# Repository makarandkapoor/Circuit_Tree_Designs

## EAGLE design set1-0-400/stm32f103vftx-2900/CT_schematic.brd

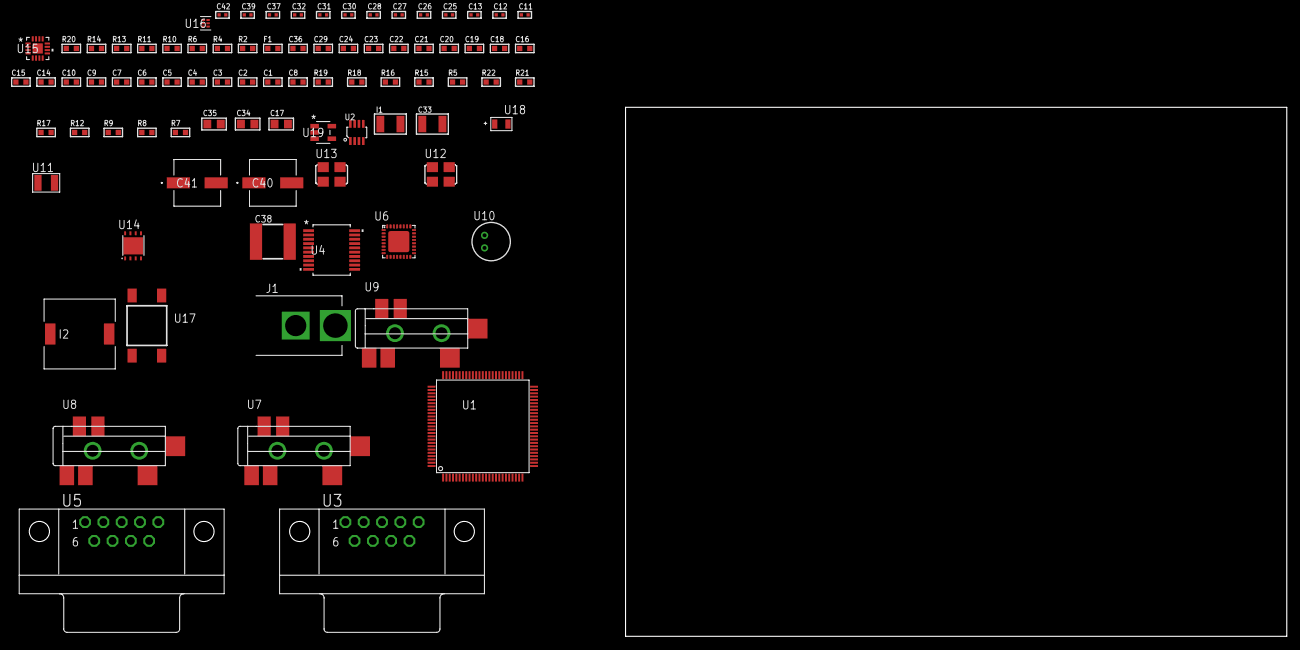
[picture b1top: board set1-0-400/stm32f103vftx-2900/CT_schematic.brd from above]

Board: 2 copper layers, 100.0 x 80.0 mm, 85 parts (0 on the bottom side), 58 nets, no tracks yet.

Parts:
C1, C10, C14, C15, C16, C18, C19, C20, C21, C22, C23, C24, C29, C36: 1e-06; C0603
C2, C3, C4, C5, C6, C7: 1e-07; C0603
C8: 4.7e-06; C0603
C9: 1e-08; C0603
C11, C12: 1e-11; C0402
C13, C25, C26, C27, C28, C37, C39: 1e-07; C0402
C17: 4.7e-06; C0805
C30, C31, C32, C42: 1e-08; C0402
C33: 1e-05; C1210
C34, C35: 1e-05; C0805
C38: 6.8e-05; 2220
C40, C41: 0.0001; EXV-9H
F1: 240.0; L0603
I1: 1.5e-05; L1210
I2: 5.2e-06; DR1040
J1: PJ-037B; PJ-037B_PACKAGE
R2, R14: 1000.0; R0603
R4: 4700.0; R0603
R5, R18, R19: 10000.0; R0603
R6: 120.0; R0603
R7, R8, R9, R12: 100000.0; R0603
R10, R11: 1270.0; R0603
R13: 200.0; R0603
R15: 20000.0; R0603
R16: 91000.0; R0603
R17: 300000.0; R0603
R20: 9100.0; R0603
R21: 680000.0; R0603
R22: 120000.0; R0603
U1: stm32f103vft7; LQFP100
U2: MAX3051EKA+T; SOT-23-8
U3, U5: 182-009-113R531; 182-009-MALE
U4: MAX3218EAP+T; SSOP-20
U6: SGTL5000XNAA3; QFN-32
U7, U8, U9: SJ-43515TS-SMT-TR
U10: WM-64PCT; WM-64PC
U11: ABS07-32.768KHZ-7-T
U12: ASFL-24.57MHZ-NCS; ASFL1
U13: ASFL1-25MHZ-NCS; ASFL1
U14: LP3878SDX-ADJ/NOPB; WSON-8
U15: LTC3601EUD#PBF; QFN-16_EP
U16: TPS3895ADRYR; SON-6
U17: 4-1437565-2; SW_4-1437565-2
U18: Q65110A2395; LGM67K-G1J2-24-Z
U19: nc7sz125m5x; NC7SZ125M5X

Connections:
CLK_CRYSTAL_U1_8: C11.1, U1.8, U11.1
CLK_CRYSTAL_U1_9: C12.1, U1.9, U11.2
CLK_U1_12: U1.12, U13.3
CLK_U6_21: U6.21, U12.3
GND: C1.2, C2.2, C3.2, C4.2, C5.2, C6.2, C7.2, C8.2, C9.2, C10.2, C11.2, C12.2, C13.2, C14.2, C15.2, C16.2, C25.2, C26.2, C27.2, C28.2, C29.2, C30.2, C31.2, C32.2, C33.2, C34.2, C35.2, C36.2, C38.1, C38.2, C39.2, C40.2, C41.2, C42.2, J1.2, R2.2, R5.2, R11.2, R14.2, R15.2, R17.2, R20.2, R22.2, U1.10, U1.19, U1.20, U1.27, U1.49, U1.74, U1.99, U2.2, U2.8, U3.5, U4.5, U4.17, U4.20, U5.5, U6.1, U6.3, U6.7, U6.EXP, U8.1, U9.1, U10.2, U12.2, U13.2, U14.3, U14.PAD, U15.1, U15.9, U15.17, U16.2, U18.C, U19.1, U19.3
NET_U1_14: R4.1, U1.14, U19.4
NET_U1_22: C9.1, C10.1, F1.1, U1.21, U1.22
NET_U1_94: R5.1, U1.94
NET_U1_98: U17.3, U17.4
NET_U2_6: R6.2, U2.6
NET_U3_2: R6.2, U2.6, U3.2
NET_U3_3: R6.1, U2.7, U3.3
NET_U4_1: I1.1, U4.1
NET_U4_2: R7.1, U4.2
NET_U4_3: R8.1, U4.3
NET_U4_4: R9.1, U4.4
NET_U4_15: C16.1, U4.15
NET_U4_16: C17.2, U4.16
NET_U4_18: C17.1, U4.18
NET_U4_19: C15.1, U4.19
NET_U5_2: U4.12, U5.2
NET_U5_3: U4.14, U5.3
NET_U5_7: U4.11, U5.7
NET_U5_8: U4.13, U5.8
NET_U6_10: C28.1, U6.10
NET_U6_29: R10.1, U6.29
NET_U6_31: R11.1, U6.31
NET_U7_1: U6.4, U7.1
NET_U7_2: U6.2, U7.2
NET_U7_5: U6.6, U7.5
NET_U8_2: C19.1, U8.2
NET_U8_5: C18.1, U8.5
NET_U9_2: C21.1, C22.1, U9.2
NET_U9_5: C20.1, U9.5
NET_U9_13: C21.2, C22.2
NET_U10_1: C23.1, C24.1, C29.1, U6.16, U10.1
NET_U10_15: C23.2, C24.2
NET_U14_1: C32.1, U14.1
NET_U14_6: R13.2, R14.1, U14.6
NET_U14_8: R12.1, U14.8
NET_U15_3: C37.2, I2.1, U15.3, U15.4
NET_U15_6: C37.1, U15.6
NET_U15_7: C36.1, U15.7, U15.12
NET_U15_10: R17.1, U15.10
NET_U15_11: R15.1, R16.1, U15.11
NET_U15_ATNET_3: I2.2, R16.2
NET_U16_1: R19.1, R20.1, U16.1
NET_U16_3: R21.2, R22.1, U16.3
NET_U16_4: R18.1, U16.4, U19.2
NET_U17_1: R2.1, U17.1, U17.2
PROC_CAN_RX: U1.70, U2.4
PROC_CAN_TX: U1.71, U2.1
PROC_I2S2_CK: U1.52, U6.24
PROC_I2S2_SD: U1.54, U6.26
PROC_I2S2_WS: U1.51, U6.23
VCC_S1_11V8: C33.1, C35.1, C40.1, C41.1, J1.1, R12.2, U14.4, U15.15, U15.16
VCC_TIER1_1V2: C25.1, C34.1, R13.1, U6.30, U14.5
VCC_TIER1_3V3: C1.1, C2.1, C3.1, C4.1, C5.1, C6.1, C7.1, C8.1, C13.1, C14.1, C26.1, C27.1, C30.1, C31.1, C38.2, C39.1, C42.1, F1.2, I1.2, I2.2, R4.2, R7.2, R8.2, R9.2, R10.2, R16.2, R18.2, R19.2, R21.1, U1.6, U1.11, U1.28, U1.50, U1.75, U1.100, U2.3, U4.6, U6.5, U6.20, U12.4, U13.4, U15.8, U16.6, U19.5

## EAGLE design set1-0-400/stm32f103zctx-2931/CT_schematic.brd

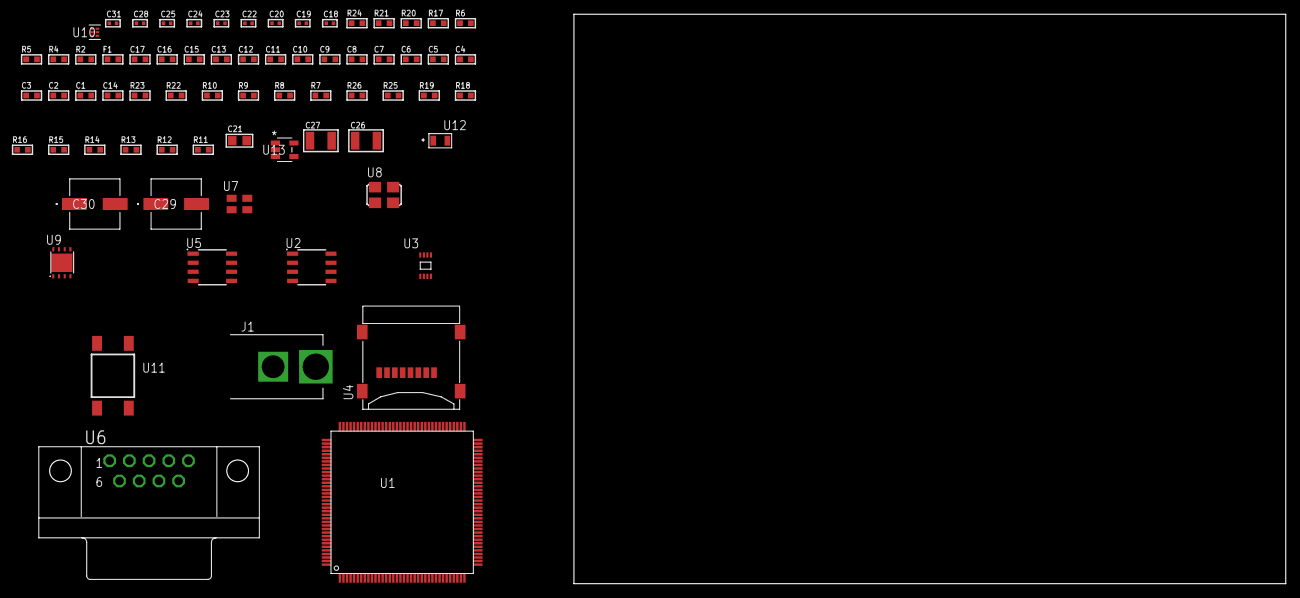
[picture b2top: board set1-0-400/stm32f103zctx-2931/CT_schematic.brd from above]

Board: 2 copper layers, 100.0 x 80.0 mm, 70 parts (0 on the bottom side), 36 nets, no tracks yet.

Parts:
C1, C17: 1e-06; C0603
C2, C3, C4, C5, C6, C7, C8, C9, C10, C11, C12, C13: 1e-07; C0603
C14: 4.7e-06; C0603
C15, C16: 1e-08; C0603
C18, C19, C23, C24, C25, C31: 1e-08; C0402
C20, C22, C28: 1e-07; C0402
C21: 1e-05; C0805
C26, C27: 1e-05; C1210
C29, C30: 0.0001; EXV-9H
F1: 240.0; L0603
J1: PJ-037B; PJ-037B_PACKAGE
R2, R21: 1000.0; R0603
R4: 4700.0; R0603
R5, R6: 2200.0; R0603
R7, R8, R9, R10, R22, R23: 10000.0; R0603
R11, R12, R13, R14, R15, R16, R19: 100000.0; R0603
R17: 120.0; R0603
R18: 470000.0; R0603
R20: 2231.0; R0603
R24: 9100.0; R0603
R25: 680000.0; R0603
R26: 120000.0; R0603
U1: stm32f103zct7; LQFP144
U2: AT25M02-SSHD-T; SOIC-8
U3: 24AA16-I/MC; TDFN-8/6MM
U4: 0472192001; MOLEX_47219-2001
U5: SN65HVD230D; SOIC-8
U6: 182-009-113R531; 182-009-MALE
U7: ASEK-32.768KHz-ECST; ASEK
U8: ASFL1-25MHZ-NCS; ASFL1
U9: LP3878SDX-ADJ/NOPB; WSON-8
U10: TPS3895ADRYR; SON-6
U11: 4-1437565-2; SW_4-1437565-2
U12: Q65110A2395; LGM67K-G1J2-24-Z
U13: nc7sz125m5x; NC7SZ125M5X

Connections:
CLK_U1_8: U1.8, U7.3
CLK_U1_23: U1.23, U8.3
GND: C1.2, C2.2, C3.2, C4.2, C5.2, C6.2, C7.2, C8.2, C9.2, C10.2, C11.2, C12.2, C13.2, C14.2, C15.2, C16.2, C17.2, C18.2, C19.2, C20.2, C21.2, C22.2, C23.2, C24.2, C25.2, C26.2, C27.2, C28.2, C29.2, C30.2, C31.2, J1.2, R2.2, R7.2, R18.2, R21.2, R24.2, R26.2, U1.16, U1.30, U1.31, U1.38, U1.51, U1.61, U1.71, U1.83, U1.94, U1.107, U1.120, U1.130, U1.143, U2.4, U3.4, U3.7, U4.6, U4.G1, U4.G2, U4.G3, U4.G4, U5.2, U6.5, U7.2, U8.2, U9.3, U9.PAD, U10.2, U12.C, U13.1, U13.3
NET_U1_25: R4.1, U1.25, U13.4
NET_U1_33: C15.1, C16.1, C17.1, F1.1, U1.32, U1.33
NET_U1_136: R5.1, U1.136, U3.6
NET_U1_137: R6.1, U1.137, U3.5
NET_U1_138: R7.1, U1.138
NET_U1_142: U11.3, U11.4
NET_U2_3: R8.1, U2.3
NET_U2_7: R10.1, U2.7
NET_U5_6: R17.2, U5.6
NET_U5_8: R18.1, U5.8
NET_U6_2: R17.2, U5.6, U6.2
NET_U6_3: R17.1, U5.7, U6.3
NET_U9_1: C25.1, U9.1
NET_U9_6: R20.2, R21.1, U9.6
NET_U9_8: R19.1, U9.8
NET_U10_1: R23.1, R24.1, U10.1
NET_U10_3: R25.2, R26.1, U10.3
NET_U10_4: R22.1, U10.4, U13.2
NET_U11_1: R2.1, U11.1, U11.2
PROC_CAN_RX: U1.103, U5.4
PROC_CAN_TX: U1.104, U5.1
PROC_SDIO_CK: R12.1, U1.113, U4.5
PROC_SDIO_CMD: R11.1, U1.116, U4.3
PROC_SDIO_D0: R13.1, U1.98, U4.7
PROC_SDIO_D1: R14.1, U1.99, U4.8
PROC_SDIO_D2: R15.1, U1.111, U4.1
PROC_SDIO_D3: R16.1, U1.112, U4.2
PROC_SPI1_MISO: U1.42, U2.2
PROC_SPI1_MOSI: U1.43, U2.5
PROC_SPI1_NSS: R9.1, U1.40, U2.1
PROC_SPI1_SCK: U1.41, U2.6
VCC_S1_14V4: C26.1, C29.1, C30.1, J1.1, R19.2, U9.4
VCC_TIER1_3V3: C1.1, C2.1, C3.1, C4.1, C5.1, C6.1, C7.1, C8.1, C9.1, C10.1, C11.1, C12.1, C13.1, C14.1, C18.1, C19.1, C20.1, C21.1, C22.1, C23.1, C24.1, C27.1, C28.1, C31.1, F1.2, R4.2, R5.2, R6.2, R8.2, R9.2, R10.2, R11.2, R12.2, R13.2, R14.2, R15.2, R16.2, R20.1, R22.2, R23.2, R25.1, U1.6, U1.17, U1.39, U1.52, U1.62, U1.72, U1.84, U1.95, U1.108, U1.121, U1.131, U1.144, U2.8, U3.8, U4.4, U5.3, U7.4, U8.4, U9.5, U10.6, U13.5

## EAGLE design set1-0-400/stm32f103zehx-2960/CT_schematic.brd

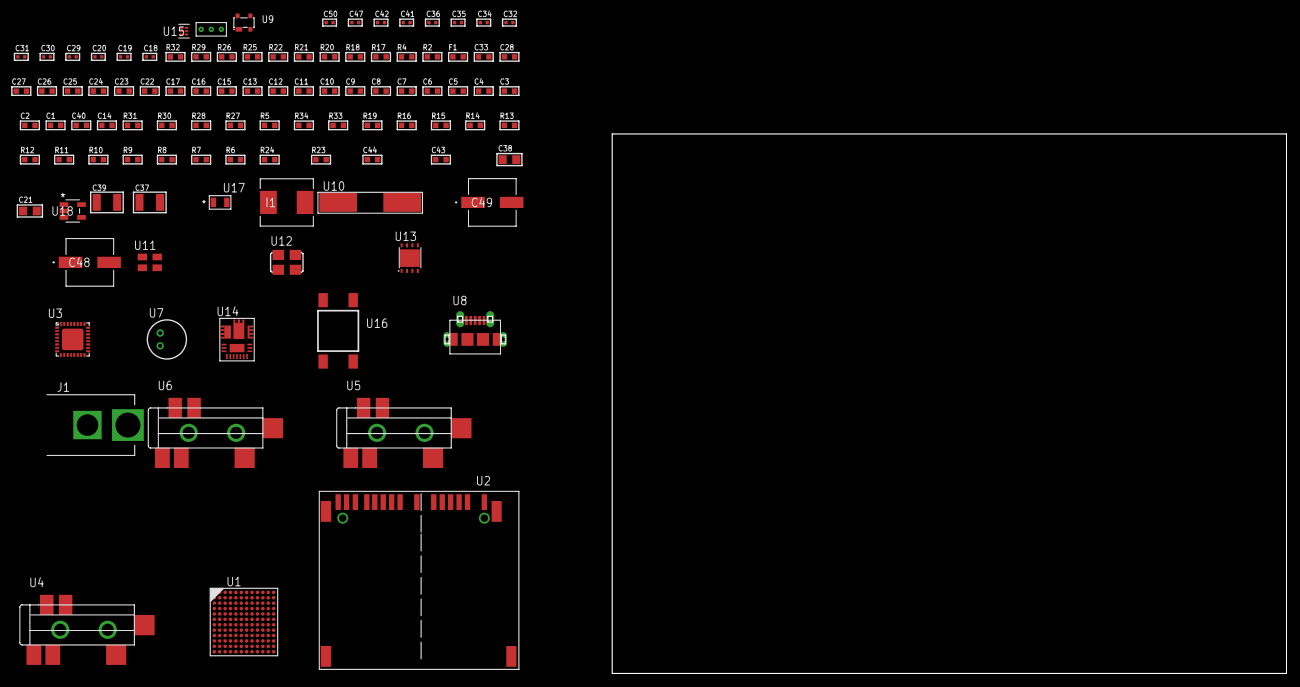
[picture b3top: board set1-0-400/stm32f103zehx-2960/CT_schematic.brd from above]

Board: 2 copper layers, 124.8 x 80.0 mm, 102 parts (0 on the bottom side), 62 nets, no tracks yet.

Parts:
C1, C17, C22, C23, C24, C25, C26, C27, C28, C33: 1e-06; C0603
C2, C3, C4, C5, C6, C7, C8, C9, C10, C11, C12, C13: 1e-07; C0603
C14: 4.7e-06; C0603
C15, C16: 1e-08; C0603
C18, C19: 1e-11; C0402
C20, C29, C30, C31, C32, C41, C42, C47: 1e-07; C0402
C21, C38: 1e-05; C0805
C34, C35, C36, C50: 1e-08; C0402
C37: 1e-05; C1210
C39: 0.0001; C1210
C40: 2.2e-06; C0603
C43: 6.9430689229727e-09; R0603
C44: 2.3669553146498e-07; R0603
C48, C49: 0.0001; EXV-9H
F1: 240.0; L0603
I1: 6.8e-07; IND25X25CZ
J1: PJ-037B; PJ-037B_PACKAGE
R2, R21: 1000.0; R0603
R4: 4700.0; R0603
R5, R30, R31: 10000.0; R0603
R6, R7, R8, R9, R10, R11, R12, R13, R14, R15, R16, R19: 100000.0; R0603
R17, R18: 1270.0; R0603
R20: 200.0; R0603
R22: 0.1; R0603
R23: 4030.2416170974; R0603
R24: 719.68600305311; R0603
R25: 75.0; R0603
R26: 130.0; R0603
R27: 39000.0; R0603
R28: 49900.0; R0603
R29: 5760.0; R0603
R32: 9100.0; R0603
R33: 680000.0; R0603
R34: 120000.0; R0603
U1: stm32f103zeh7; LFBGA144
U2: 10100565
U3: SGTL5000XNAA3; QFN-32
U4, U5, U6: SJ-43515TS-SMT-TR
U7: WM-64PCT; WM-64PC
U8: 47590-0001; MICRO_USB_AB
U9: prtr5v0u2ax; SOT143B
U10: ABLS-25.000MHZ-B2F-T
U11: ASEK-32.768KHz-ECST; ASEK
U12: ASFL-24.57MHZ-NCS; ASFL1
U13: LP3878SDX-ADJ/NOPB; WSON-8
U14: IR3899MTR1PBF
U15: TPS3895ADRYR; SON-6
U16: 4-1437565-2; SW_4-1437565-2
U17: Q65110A2395; LGM67K-G1J2-24-Z
U18: nc7sz125m5x; NC7SZ125M5X
U19: Dummy; DUMMY_PACKAGE_198

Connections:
CLK_CRYSTAL_U1_D1: C18.1, U1.D1, U10.1
CLK_CRYSTAL_U1_E1: C19.1, U1.E1, U10.2
CLK_U1_B1: U1.B1, U11.3
CLK_U3_21: U3.21, U12.3
GND: C1.2, C2.2, C3.2, C4.2, C5.2, C6.2, C7.2, C8.2, C9.2, C10.2, C11.2, C12.2, C13.2, C14.2, C15.2, C16.2, C17.2, C18.2, C19.2, C20.2, C21.2, C29.2, C30.2, C31.2, C32.2, C33.2, C34.2, C35.2, C36.2, C37.2, C38.2, C40.2, C41.2, C42.2, C47.2, C48.2, C49.2, C50.2, J1.2, R2.2, R5.2, R18.2, R21.2, R22.1, R22.2, R24.2, R27.2, R29.2, R32.2, R34.2, U1.D2, U1.E5, U1.E6, U1.E7, U1.G4, U1.G8, U1.G9, U1.G10, U1.H5, U1.H6, U1.H7, U1.J1, U1.K1, U2.6, U2.10, U2.12, U2.16, U2.17, U2.20, U2.21, U3.1, U3.3, U3.7, U3.EXP, U5.1, U6.1, U7.2, U8.5, U8.6, U8.7, U8.8, U8.9, U9.1, U11.2, U12.2, U13.3, U13.PAD, U14.4, U14.11, U14.17, U15.2, U17.C, U18.1, U18.3, U19.1
NET_U1_D5: R5.1, U1.D5
NET_U1_F1: R4.1, U1.F1, U18.4
NET_U1_M1: C15.1, C16.1, C17.1, F1.1, U1.L1, U1.M1
NET_U1_M10: U16.3, U16.4
NET_U2_1: R8.1, U2.1
NET_U2_2: R7.1, U2.2
NET_U2_18: U2.18, U2.19
NET_U3_10: C32.1, U3.10
NET_U3_29: R17.1, U3.29
NET_U3_31: R18.1, U3.31
NET_U4_1: U3.4, U4.1
NET_U4_2: U3.2, U4.2
NET_U4_5: U3.6, U4.5
NET_U5_2: C23.1, U5.2
NET_U5_5: C22.1, U5.5
NET_U6_2: C25.1, C26.1, U6.2
NET_U6_5: C24.1, U6.5
NET_U6_13: C25.2, C26.2
NET_U7_1: C27.1, C28.1, C33.1, U3.16, U7.1
NET_U7_15: C27.2, C28.2
NET_U9_4: U8.1, U9.4
NET_U13_1: C36.1, U13.1
NET_U13_6: R20.2, R21.1, U13.6
NET_U13_8: R19.1, U13.8
NET_U14_1: C43.1, R23.1, R24.1, R25.1, R26.1, U14.1, U14.8
NET_U14_2: C42.1, U14.2
NET_U14_3: C43.2, C44.1, C44.2, U14.3
NET_U14_5: R27.1, U14.5
NET_U14_10: C40.1, U14.10
NET_U14_12: C39.1, I1.1, U14.12
NET_U14_14: C39.2, U14.14
NET_U14_15: R28.1, R29.1, U14.15
NET_U14_ATNET_3: I1.2, R23.2
NET_U14_ATNET_4: C44.2, R25.2
NET_U15_1: R31.1, R32.1, U15.1
NET_U15_3: R33.2, R34.1, U15.3
NET_U15_4: R30.1, U15.4, U18.2
NET_U16_1: R2.1, U16.1, U16.2
PROC_I2S2_CK: U1.M12, U3.24
PROC_I2S2_SD: U1.L12, U3.26
PROC_I2S2_WS: U1.M11, U3.23
PROC_SDIO_CK: R6.1, U1.C10, U2.8
PROC_SDIO_D0: R9.1, U1.F11, U2.4
PROC_SDIO_D1: R10.1, U1.E11, U2.3
PROC_SDIO_D2: R11.1, U1.B11, U2.15
PROC_SDIO_D3: R12.1, U1.B10, U2.14
PROC_SDIO_D4: R13.1, U1.C5, U2.13
PROC_SDIO_D5: R14.1, U1.B5, U2.11
PROC_SDIO_D6: R15.1, U1.G12, U2.7
PROC_SDIO_D7: R16.1, U1.F12, U2.5
PROC_TIM1_CH2: U1.D12, U19.2
PROC_TIM1_CH2N: U1.J7, U19.3
PROC_USB_DM: U8.2, U9.3
PROC_USB_DP: U8.3, U9.2
VCC_S1_15V2: C37.1, C41.1, C48.1, C49.1, J1.1, R19.2, R28.2, U13.4, U14.9
VCC_TIER1_1V2: C29.1, C38.1, R20.1, U3.30, U13.5
VCC_TIER1_3V3: C1.1, C2.1, C3.1, C4.1, C5.1, C6.1, C7.1, C8.1, C9.1, C10.1, C11.1, C12.1, C13.1, C14.1, C20.1, C21.1, C30.1, C31.1, C34.1, C35.1, C47.1, C50.1, F1.2, I1.2, R4.2, R6.2, R7.2, R8.2, R9.2, R10.2, R11.2, R12.2, R13.2, R14.2, R15.2, R16.2, R17.2, R23.2, R30.2, R31.2, R33.1, U1.C2, U1.D3, U1.F4, U1.F5, U1.F6, U1.F7, U1.F8, U1.F9, U1.F10, U1.G5, U1.G6, U1.G7, U2.9, U3.5, U3.20, U11.4, U12.4, U15.6, U18.5

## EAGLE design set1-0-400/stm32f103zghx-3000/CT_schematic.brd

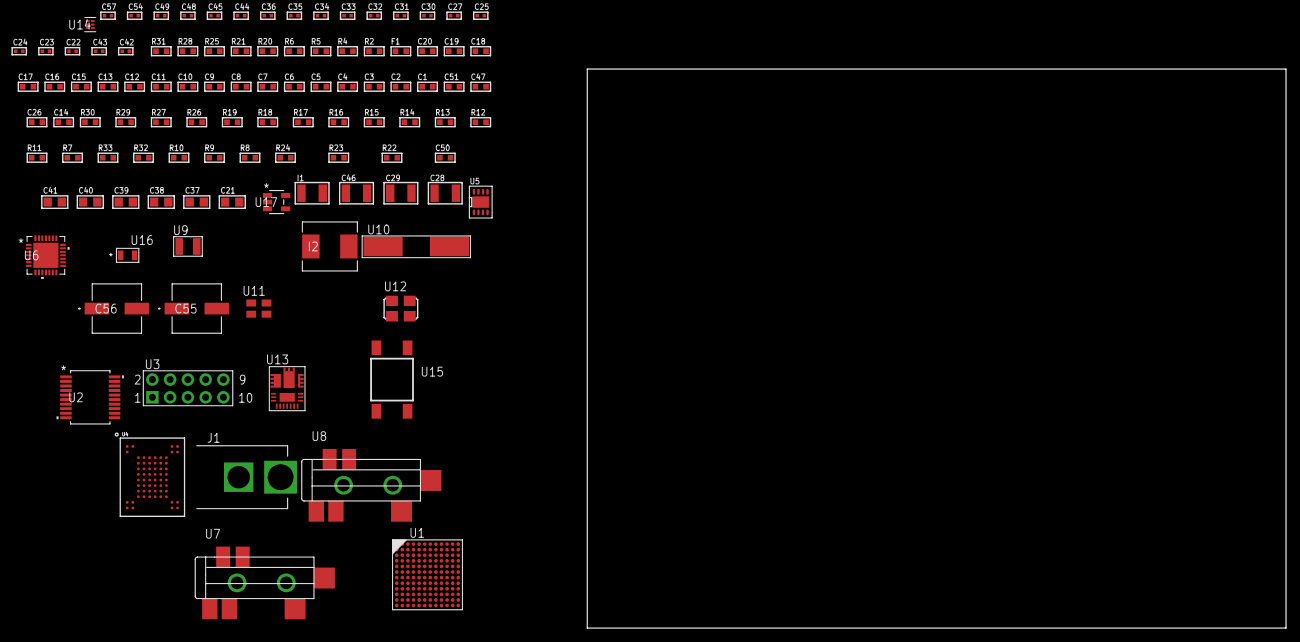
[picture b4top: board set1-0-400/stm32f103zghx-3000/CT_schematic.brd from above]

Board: 2 copper layers, 100.0 x 80.0 mm, 107 parts (0 on the bottom side), 64 nets, no tracks yet.

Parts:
C1, C17, C18, C19, C20: 1e-06; C0603
C2, C3, C4, C5, C6, C7, C8, C9, C10, C11, C12, C13: 1e-07; C0603
C14: 4.7e-06; C0603
C15, C16: 1e-08; C0603
C21: 4.7e-06; C0805
C22, C23, C24, C25, C27, C32, C33, C34, C35, C36, C48, C49, C54: 1e-07; C0402
C26, C47: 2.2e-06; C0603
C28, C29: 2.2e-05; C1210
C30, C31: 1e-09; C0402
C37, C38, C39, C40, C41: 1e-05; C0805
C42, C43: 2.2e-11; C0402
C44, C45, C57: 1e-08; C0402
C46: 0.0001; C1210
C50: 7.8444498006919e-09; R0603
C51: 2.7e-07; C0603
C55, C56: 0.0001; EXV-9H
F1: 240.0; L0603
I1: 1.5e-05; L1210
I2: 6.8e-07; IND25X25CZ
J1: PJ-037B; PJ-037B_PACKAGE
R2: 1000.0; R0603
R4: 4700.0; R0603
R5, R6: 2200.0; R0603
R7, R11, R12, R13, R14, R15, R16, R29, R30: 10000.0; R0603
R8, R9, R10: 100000.0; R0603
R17, R18, R19: 47000.0; R0603
R20: 680.0; R0603
R21: 0.1; R0603
R22: 4030.2416170974; R0603
R23: 719.68600305311; R0603
R24: 64.984347826087; R0603
R25: 130.0; R0603
R26: 39000.0; R0603
R27: 49900.0; R0603
R28: 5600.0; R0603
R31: 9100.0; R0603
R32: 680000.0; R0603
R33: 120000.0; R0603
U1: stm32f103zgh7; LFBGA144
U2: MAX3218EAP+T; SSOP-20
U3: HTSS-105-01-G-D
U4: mt29f4g08abadah4; VFBGA-63
U5: PCF85063TP/1Z; SON-8
U6: WM8731CLSEFL; QFN-28
U7, U8: SJ-43515TS-SMT-TR
U9: ABS07-32.768KHZ-7-T
U10: ABLS-12.288MHZ-B4-T
U11: ASEK-32.768KHz-ECST; ASEK
U12: ASFL1-25MHZ-NCS; ASFL1
U13: IR3899MTR1PBF
U14: TPS3895ADRYR; SON-6
U15: 4-1437565-2; SW_4-1437565-2
U16: Q65110A2395; LGM67K-G1J2-24-Z
U17: nc7sz125m5x; NC7SZ125M5X

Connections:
CLK_CRYSTAL_U5_1: U5.1, U9.1
CLK_CRYSTAL_U5_2: U5.2, U9.2
CLK_CRYSTAL_U6_1: C42.1, U6.1, U10.1
CLK_CRYSTAL_U6_2: C43.1, U6.2, U10.2
CLK_U1_B1: U1.B1, U11.3
CLK_U1_D1: U1.D1, U12.3
GND: C1.2, C2.2, C3.2, C4.2, C5.2, C6.2, C7.2, C8.2, C9.2, C10.2, C11.2, C12.2, C13.2, C14.2, C15.2, C16.2, C17.2, C18.2, C19.2, C20.2, C22.2, C23.2, C24.2, C25.2, C26.2, C27.2, C31.2, C32.2, C33.2, C34.2, C35.2, C36.2, C37.2, C38.2, C39.2, C40.2, C41.2, C42.2, C43.2, C44.2, C45.2, C47.2, C48.2, C49.2, C54.2, C55.2, C56.2, C57.2, J1.2, R2.2, R7.2, R17.2, R18.2, R19.2, R21.1, R21.2, R23.2, R26.2, R28.2, R31.2, R33.2, U1.D2, U1.E5, U1.E6, U1.E7, U1.G4, U1.G8, U1.G9, U1.G10, U1.H5, U1.H6, U1.H7, U1.J1, U1.K1, U2.5, U2.17, U2.20, U3.9, U4.C5, U4.F7, U4.K3, U4.K8, U5.4, U5.PAD, U6.4, U6.15, U6.19, U6.25, U6.26, U6.29, U7.1, U8.1, U11.2, U12.2, U13.4, U13.11, U13.17, U14.2, U16.C, U17.1, U17.3
NET_U1_B5: R6.1, U1.B5, U5.5
NET_U1_C5: R5.1, U1.C5, U5.6
NET_U1_D5: R7.1, U1.D5
NET_U1_F1: R4.1, U1.F1, U17.4
NET_U1_M1: C15.1, C16.1, C17.1, F1.1, U1.L1, U1.M1
NET_U1_M10: U15.3, U15.4
NET_U2_1: I1.1, U2.1
NET_U2_2: R8.1, U2.2
NET_U2_3: R9.1, U2.3
NET_U2_4: R10.1, U2.4
NET_U2_15: C20.1, U2.15
NET_U2_16: C21.2, U2.16
NET_U2_18: C21.1, U2.18
NET_U2_19: C19.1, U2.19
NET_U3_3: U2.12, U3.3
NET_U3_4: U2.11, U3.4
NET_U3_5: U2.14, U3.5
NET_U3_6: U2.13, U3.6
NET_U4_C3: R15.1, U4.C3
NET_U4_C8: R11.1, U4.C8
NET_U5_3: R16.1, U5.3
NET_U6_20: C36.1, C41.1, U6.20
NET_U7_2: C29.1, R18.1, U7.2
NET_U7_5: C28.1, R17.1, U7.5
NET_U8_5: C30.1, C31.1, R19.1, R20.1, U8.5
NET_U13_1: C50.1, R22.1, R23.1, R24.1, R25.1, U13.1, U13.8
NET_U13_2: C49.1, U13.2
NET_U13_3: C50.2, C51.1, C51.2, U13.3
NET_U13_5: R26.1, U13.5
NET_U13_10: C47.1, U13.10
NET_U13_12: C46.1, I2.1, U13.12
NET_U13_14: C46.2, U13.14
NET_U13_15: R27.1, R28.1, U13.15
NET_U13_ATNET_3: I2.2, R22.2
NET_U13_ATNET_4: C51.2, R24.2
NET_U14_1: R30.1, R31.1, U14.1
NET_U14_3: R32.2, R33.1, U14.3
NET_U14_4: R29.1, U14.4, U17.2
NET_U15_1: R2.1, U15.1, U15.2
PROC_FSMC_D0: U1.K11, U4.H4
PROC_FSMC_D1: U1.K12, U4.J4
PROC_FSMC_D2: U1.E10, U4.K4
PROC_FSMC_D3: U1.D10, U4.K5
PROC_FSMC_D4: U1.M7, U4.K6
PROC_FSMC_D5: U1.L7, U4.J7
PROC_FSMC_D6: U1.K7, U4.K7
PROC_FSMC_D7: U1.J7, U4.J8
PROC_FSMC_NCE2: R12.1, U1.A9, U4.C6
PROC_FSMC_NOE: R14.1, U1.C9, U4.D4
PROC_FSMC_NWE: R13.1, U1.B9, U4.C7
PROC_I2S2_CK: U1.M12, U6.7
PROC_I2S2_SD: U1.L12, U6.8
PROC_I2S2_WS: U1.M11, U6.9, U6.11
PROC_UART4_RX: U1.B10, U2.9
PROC_UART4_TX: U1.B11, U2.7
VCC_S1_16V1: C48.1, C55.1, C56.1, J1.1, R27.2, U13.9
VCC_TIER1_3V3: C1.1, C2.1, C3.1, C4.1, C5.1, C6.1, C7.1, C8.1, C9.1, C10.1, C11.1, C12.1, C13.1, C14.1, C18.1, C22.1, C23.1, C24.1, C25.1, C26.1, C27.1, C32.1, C33.1, C34.1, C35.1, C37.1, C38.1, C39.1, C40.1, C44.1, C45.1, C54.1, C57.1, F1.2, I1.2, I2.2, R4.2, R5.2, R6.2, R8.2, R9.2, R10.2, R11.2, R12.2, R13.2, R14.2, R15.2, R16.2, R22.2, R29.2, R30.2, R32.1, U1.C2, U1.D3, U1.F4, U1.F5, U1.F6, U1.F7, U1.F8, U1.F9, U1.F10, U1.G5, U1.G6, U1.G7, U2.6, U4.D3, U4.G4, U4.H8, U4.J6, U5.8, U6.3, U6.5, U6.12, U6.18, U11.4, U12.4, U14.6, U17.5

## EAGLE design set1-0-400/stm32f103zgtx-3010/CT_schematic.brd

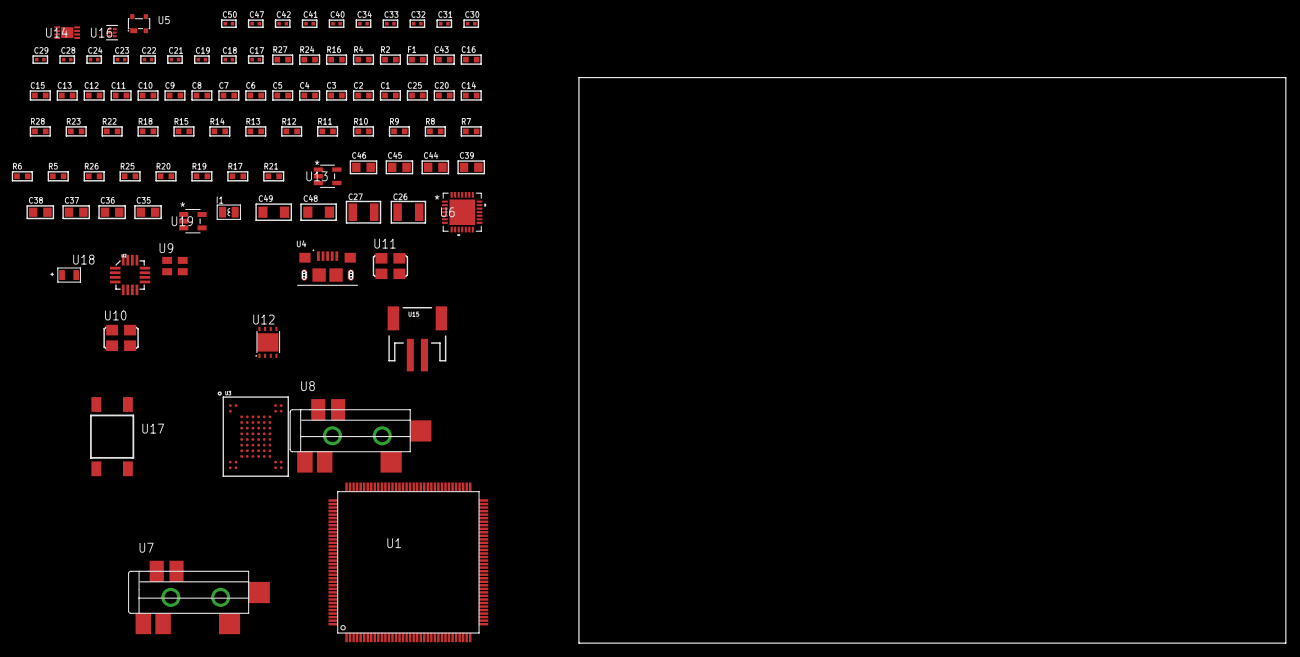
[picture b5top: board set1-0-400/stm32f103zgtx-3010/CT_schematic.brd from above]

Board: 2 copper layers, 97 parts (0 on the bottom side), 42 nets, no tracks yet.

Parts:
C1, C16, C43: 1e-06; C0603
C2, C3, C4, C5, C6, C7, C8, C9, C10, C11, C12, C13: 1e-07; C0603
C14: 4.7e-06; C0603
C15: 1e-08; C0603
C17, C18, C19, C40, C41, C42, C50: 1e-08; C0402
C20: 4.7e-07; C0603
C21, C22, C23, C24, C30, C31, C32, C33, C34, C47: 1e-07; C0402
C25: 2.2e-06; C0603
C26, C27: 2.2e-05; C1210
C28, C29: 1e-09; C0402
C35, C36, C37, C38, C39, C44, C45, C46: 1e-05; C0805
C48, C49: 1e-05; C1206
F1: 240.0; L0603
I1: 1.5e-06; L0806
R2: 1000.0; R0603
R4: 4700.0; R0603
R5, R6, R7, R8, R9, R10, R11, R12, R22, R23, R28: 10000.0; R0603
R13, R14, R15: 47000.0; R0603
R16: 680.0; R0603
R17, R19: 100000.0; R0603
R18: 36000.0; R0603
R20: 220000.0; R0603
R21: 1000000.0; R0603
R24: 9100.0; R0603
R25: 680000.0; R0603
R26: 120000.0; R0603
R27: 2000.0; R0603
U1: stm32f103zgt6; LQFP144
U2: l3g4200d; LGA-16
U3: mt29f4g08abbdah4; VFBGA-63
U4: 10118193-0001LF; FCI_10118193-0001LF
U5: prtr5v0u2ax; SOT143B
U6: WM8731CLSEFL; QFN-28
U7, U8: SJ-43515TS-SMT-TR
U9: ASEK-32.768KHz-ECST; ASEK
U10: ASFL1-12.288MHZ-EC-T; ASFL1
U11: ASFL1-25MHZ-NCS; ASFL1
U12: LP2951ACSDX/NOPB; WSON-8
U13: ltc3406es5; TSOT-23-5
U14: MCP73831T-2ACI/MC; DFN8_2X3MC
U15: S2B-PH-SM4-TB(LF)(SN); JST-2-SMD
U16: TPS3895ADRYR; SON-6
U17: 4-1437565-2; SW_4-1437565-2
U18: Q65110A2395; LGM67K-G1J2-24-Z
U19: nc7sz125m5x; NC7SZ125M5X

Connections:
CLK_U1_8: U1.8, U9.3
CLK_U1_23: U1.23, U11.3
CLK_U6_1: U6.1, U10.3
GND: C1.2, C2.2, C3.2, C4.2, C5.2, C6.2, C7.2, C8.2, C9.2, C10.2, C11.2, C12.2, C13.2, C14.2, C15.2, C16.2, C17.2, C18.2, C19.2, C21.2, C22.2, C23.2, C24.2, C25.2, C29.2, C30.2, C31.2, C32.2, C33.2, C34.2, C35.2, C36.2, C37.2, C38.2, C39.2, C40.2, C41.2, C42.2, C43.2, C44.2, C45.2, C46.1, C46.2, C47.2, C48.2, C49.2, C50.2, R2.2, R5.2, R6.1, R6.2, R13.2, R14.2, R15.2, R19.2, R20.2, R24.2, R26.2, R27.2, U1.16, U1.30, U1.31, U1.38, U1.51, U1.61, U1.71, U1.83, U1.94, U1.107, U1.120, U1.130, U1.143, U2.8, U2.9, U2.10, U2.11, U2.12, U2.13, U3.C5, U3.F7, U3.K3, U3.K8, U4.5, U4.6, U4.7, U4.8, U4.9, U5.1, U6.4, U6.15, U6.19, U6.25, U6.26, U6.29, U7.1, U8.1, U9.2, U10.2, U11.2, U12.3, U12.4, U12.PAD, U13.2, U14.6, U14.9, U15.2, U16.2, U18.C, U19.1, U19.3
INPUT_USBPOWER_5V: C48.1, R28.2, U4.1, U5.4, U14.1, U14.2
NET_U1_25: R4.1, U1.25, U19.4
NET_U1_33: C15.1, C16.1, F1.1, U1.32, U1.33
NET_U1_138: R5.1, U1.138
NET_U1_142: U17.3, U17.4
NET_U2_14: C19.1, C20.1, U2.14
NET_U3_C3: R12.1, U3.C3
NET_U3_C6: R9.1, U3.C6
NET_U3_C7: R10.1, U3.C7
NET_U3_C8: R8.1, U3.C8
NET_U3_D4: R11.1, U3.D4
NET_U6_20: C34.1, C39.1, U6.20
NET_U7_2: C27.1, R14.1, U7.2
NET_U7_5: C26.1, R13.1, U7.5
NET_U8_5: C28.1, C29.1, R15.1, R16.1, U8.5
NET_U12_5: R17.1, U12.5
NET_U12_7: R18.2, R19.1, U12.7
NET_U13_3: I1.1, U13.3
NET_U13_5: R20.1, R21.1, U13.5
NET_U13_ATNET_3: I1.2, R21.2
NET_U14_5: R28.1, U14.5
NET_U14_8: R27.1, U14.8
NET_U16_1: R23.1, R24.1, U16.1
NET_U16_3: R25.2, R26.1, U16.3
NET_U16_4: R22.1, U16.4, U19.2
NET_U17_1: R2.1, U17.1, U17.2
PROC_I2S2_CK: U1.74, U6.7
PROC_I2S2_SD: U1.76, U6.8
PROC_I2S2_WS: U1.73, U6.9, U6.11
PROC_SPI1_MISO: U1.42, U2.4
PROC_SPI1_MOSI: U1.43, U2.3
PROC_SPI1_NSS: R7.1, U1.40, U2.5
PROC_SPI1_SCK: U1.41, U2.2
PROC_USB_DM: U1.103, U4.2, U5.3
PROC_USB_DP: U1.104, U4.3, U5.2
VCC_S1_3V7: C43.1, C45.1, C49.1, U12.8, U13.4, U14.3, U14.4, U15.1
VCC_TIER1_1V8: C21.1, C22.1, C23.1, C24.1, C25.1, C30.1, C32.1, C33.1, C35.1, C37.1, C38.1, C44.1, C50.1, R8.2, R9.2, R10.2, R11.2, R12.2, R17.2, R18.1, U3.D3, U3.G4, U3.H8, U3.J6, U6.5, U6.12, U6.18, U12.1, U19.5
VCC_TIER1_3V3: C1.1, C2.1, C3.1, C4.1, C5.1, C6.1, C7.1, C8.1, C9.1, C10.1, C11.1, C12.1, C13.1, C14.1, C17.1, C18.1, C31.1, C36.1, C40.1, C41.1, C42.1, C46.2, C47.1, F1.2, I1.2, R4.2, R7.2, R21.2, R22.2, R23.2, R25.1, U1.6, U1.17, U1.39, U1.52, U1.62, U1.72, U1.84, U1.95, U1.108, U1.121, U1.131, U1.144, U2.1, U2.15, U2.16, U6.3, U9.4, U10.4, U11.4, U16.6

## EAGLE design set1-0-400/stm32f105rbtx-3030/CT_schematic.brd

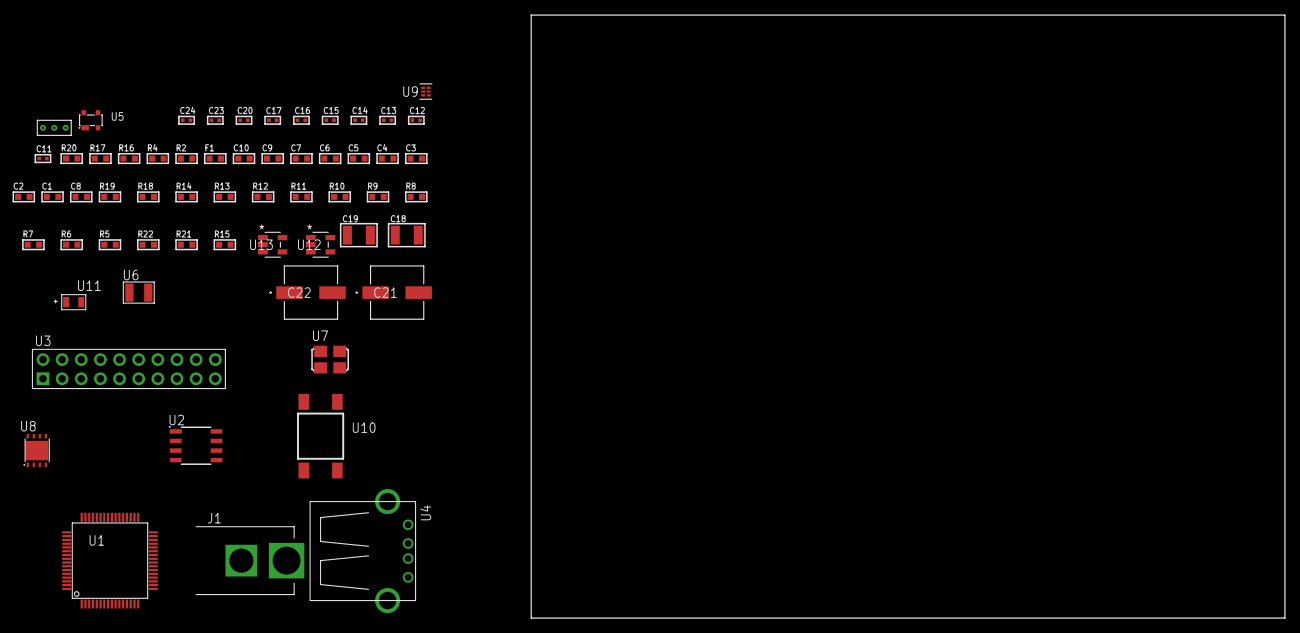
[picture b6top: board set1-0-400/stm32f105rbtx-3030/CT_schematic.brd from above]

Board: 2 copper layers, 100.0 x 80.0 mm, 60 parts (0 on the bottom side), 35 nets, no tracks yet.

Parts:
C1, C10: 1e-06; C0603
C2, C3, C4, C5, C6, C7: 1e-07; C0603
C8: 4.7e-06; C0603
C9: 1e-08; C0603
C11, C12: 1e-11; C0402
C13, C16, C17, C23, C24: 1e-08; C0402
C14, C15, C20: 1e-07; C0402
C18, C19: 1e-05; C1210
C21, C22: 0.0001; EXV-9H
F1: 240.0; L0603
J1: PJ-037B; PJ-037B_PACKAGE
R2, R17: 1000.0; R0603
R4: 4700.0; R0603
R5, R6, R7, R8, R9, R10, R11, R12, R13, R14, R18, R19: 10000.0; R0603
R15: 100000.0; R0603
R16: 2231.0; R0603
R20: 9100.0; R0603
R21: 680000.0; R0603
R22: 120000.0; R0603
U1: stm32f105rbt7; LQFP64
U2: AT25080B-SSHL-T; SOIC-8
U3: TST-110-05-T-D-RA
U4: 61400416021; USB-A-H
U5: prtr5v0u2ax; SOT143B
U6: ABS07-32.768KHZ-7-T
U7: ASFL1-25MHZ-NCS; ASFL1
U8: LP3878SDX-ADJ/NOPB; WSON-8
U9: TPS3895ADRYR; SON-6
U10: 4-1437565-2; SW_4-1437565-2
U11: Q65110A2395; LGM67K-G1J2-24-Z
U12, U13: nc7sz125m5x; NC7SZ125M5X
U14: Dummy; DUMMY_PACKAGE_129

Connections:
CLK_CRYSTAL_U1_3: C11.1, U1.3, U6.1
CLK_CRYSTAL_U1_4: C12.1, U1.4, U6.2
CLK_U1_5: U1.5, U7.3
GND: C1.2, C2.2, C3.2, C4.2, C5.2, C6.2, C7.2, C8.2, C9.2, C10.2, C11.2, C12.2, C13.2, C14.2, C15.2, C16.2, C17.2, C18.2, C19.2, C20.2, C21.2, C22.2, C23.2, C24.2, J1.2, R2.2, R5.2, R14.2, R17.2, R20.2, R22.2, U1.12, U1.18, U1.31, U1.47, U1.63, U2.4, U3.4, U3.6, U3.8, U3.10, U3.12, U3.14, U3.16, U3.18, U3.20, U4.4, U4.5, U4.6, U5.1, U7.2, U8.3, U8.PAD, U9.2, U11.C, U12.2, U12.3, U13.1, U13.3, U14.1
NET_U1_7: R4.1, U1.7, U13.4
NET_U1_13: C9.1, C10.1, F1.1, U1.13
NET_U1_60: R5.1, U1.60
NET_U1_62: U10.3, U10.4
NET_U2_3: R6.1, U2.3
NET_U2_7: R8.1, U2.7
NET_U3_3: R9.1, U3.3
NET_U3_7: R11.1, U3.7
NET_U3_9: R12.1, U3.9
NET_U3_19: R14.1, U3.19
NET_U8_1: C17.1, U8.1
NET_U8_6: R16.2, R17.1, U8.6
NET_U8_8: R15.1, U8.8
NET_U9_1: R19.1, R20.1, U9.1
NET_U9_3: R21.2, R22.1, U9.3
NET_U9_4: R18.1, U9.4, U12.4, U13.2
NET_U10_1: R2.1, U10.1, U10.2
PROC_ADC1_IN1: U1.15, U14.3
PROC_ADC1_IN2: U1.16, U14.2
PROC_SPI1_MISO: U1.22, U2.2
PROC_SPI1_MOSI: U1.23, U2.5
PROC_SPI1_NSS: R7.1, U1.20, U2.1
PROC_SPI1_SCK: U1.21, U2.6
PROC_SYS_JTDI: R10.1, U1.50, U3.5
PROC_SYS_JTDO: U1.55, U3.13
PROC_USB_OTG_FS_DM: U1.44, U4.2, U5.3
PROC_USB_OTG_FS_DP: U1.45, U4.3, U5.2
PROC_USB_OTG_FS_VBUS: U1.42, U4.1, U5.4
RST_OUT_U3_SRESET_B: R13.1, U3.15, U12.1
VCC_S1_14V5: C18.1, C21.1, C22.1, J1.1, R15.2, U8.4
VCC_TIER1_3V3: C1.1, C2.1, C3.1, C4.1, C5.1, C6.1, C7.1, C8.1, C13.1, C14.1, C15.1, C16.1, C19.1, C20.1, C23.1, C24.1, F1.2, R4.2, R6.2, R7.2, R8.2, R9.2, R10.2, R11.2, R12.2, R13.2, R16.1, R18.2, R19.2, R21.1, U1.1, U1.19, U1.32, U1.48, U1.64, U2.8, U3.1, U3.2, U7.4, U8.5, U9.6, U12.5, U13.5

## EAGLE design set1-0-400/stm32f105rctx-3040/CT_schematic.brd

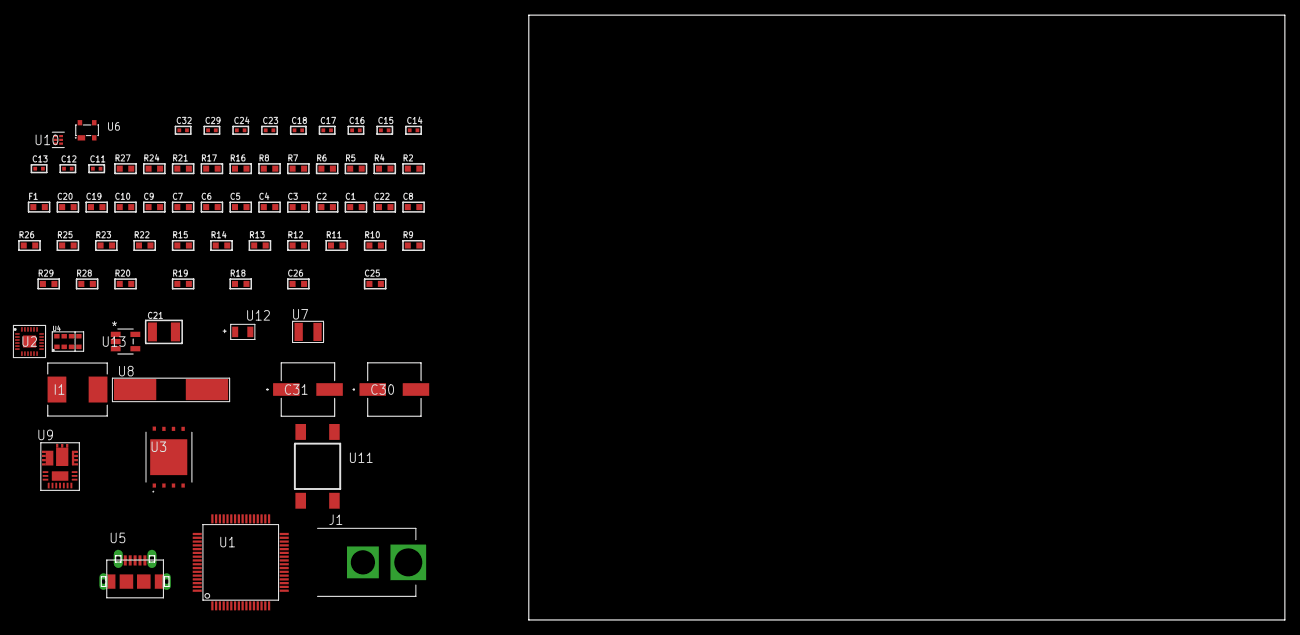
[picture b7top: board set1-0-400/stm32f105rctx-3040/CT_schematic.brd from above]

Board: 2 copper layers, 156.5 x 80.0 mm, 73 parts (0 on the bottom side), 46 nets, no tracks yet.

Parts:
C1, C10, C19, C20: 1e-06; C0603
C2, C3, C4, C5, C6, C7: 1e-07; C0603
C8: 4.7e-06; C0603
C9: 1e-08; C0603
C11, C12, C13, C14: 1e-11; C0402
C15, C16, C23, C24, C29: 1e-07; C0402
C17, C18, C32: 1e-08; C0402
C21: 0.0001; C1210
C22: 2.2e-06; C0603
C25: 8.8006443804346e-09; R0603
C26: 3.0002196751482e-07; R0603
C30, C31: 0.0001; EXV-9H
F1: 240.0; L0603
I1: 6.8e-07; IND25X25CZ
J1: PJ-037B; PJ-037B_PACKAGE
R2: 1000.0; R0603
R4: 4700.0; R0603
R5, R6, R7, R8: 2200.0; R0603
R9, R10, R11, R12, R13, R14, R15, R25, R26: 10000.0; R0603
R16: 22.0; R0603
R17: 0.1; R0603
R18: 4030.2416170974; R0603
R19: 719.68600305311; R0603
R20: 57.923764705882; R0603
R21: 130.0; R0603
R22: 39000.0; R0603
R23: 49900.0; R0603
R24: 5100.0; R0603
R27: 9100.0; R0603
R28: 680000.0; R0603
R29: 120000.0; R0603
U1: stm32f105rct6; LQFP64
U2: MPU-9250; QFN24_2
U3: S25FL128SDPNFI001; WNG008
U4: TMD27711; SMD-8
U5: 47590-0001; MICRO_USB_AB
U6: prtr5v0u2ax; SOT143B
U7: ABS07-32.768KHZ-7-T
U8: ABLS-25.000MHZ-B2F-T
U9: IR3899MTR1PBF
U10: TPS3895ADRYR; SON-6
U11: 4-1437565-2; SW_4-1437565-2
U12: Q65110A2395; LGM67K-G1J2-24-Z
U13: nc7sz125m5x; NC7SZ125M5X

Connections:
CLK_CRYSTAL_U1_3: C11.1, U1.3, U7.1
CLK_CRYSTAL_U1_4: C12.1, U1.4, U7.2
CLK_CRYSTAL_U1_5: C13.1, U1.5, U8.1
CLK_CRYSTAL_U1_6: C14.1, U1.6, U8.2
GND: C1.2, C2.2, C3.2, C4.2, C5.2, C6.2, C7.2, C8.2, C9.2, C10.2, C11.2, C12.2, C13.2, C14.2, C15.2, C16.2, C17.2, C18.2, C19.2, C20.2, C22.2, C23.2, C24.2, C29.2, C30.2, C31.2, C32.2, J1.2, R2.2, R9.2, R17.1, R17.2, R19.2, R22.2, R24.2, R27.2, R29.2, U1.12, U1.18, U1.31, U1.47, U1.63, U2.18, U2.20, U2.25, U3.4, U3.PAD, U4.3, U5.5, U5.6, U5.7, U5.8, U5.9, U6.1, U9.4, U9.11, U9.17, U10.2, U12.C, U13.1, U13.3
NET_U1_7: R4.1, U1.7, U13.4
NET_U1_13: C9.1, C10.1, F1.1, U1.13
NET_U1_29: R7.1, U1.29, U4.2
NET_U1_30: R8.1, U1.30, U4.8
NET_U1_58: R5.1, U1.58, U2.23
NET_U1_59: R6.1, U1.59, U2.24
NET_U1_60: R9.1, U1.60
NET_U1_62: U11.3, U11.4
NET_U2_9: R11.1, U2.9
NET_U2_10: C15.1, U2.10
NET_U2_22: R10.1, U2.22
NET_U3_3: R12.1, U3.3
NET_U3_7: R14.1, U3.7
NET_U4_4: C20.1, R16.1, U4.4
NET_U4_7: R15.1, U4.7
NET_U9_1: C25.1, R18.1, R19.1, R20.1, R21.1, U9.1, U9.8
NET_U9_2: C24.1, U9.2
NET_U9_3: C25.2, C26.1, C26.2, U9.3
NET_U9_5: R22.1, U9.5
NET_U9_10: C22.1, U9.10
NET_U9_12: C21.1, I1.1, U9.12
NET_U9_14: C21.2, U9.14
NET_U9_15: R23.1, R24.1, U9.15
NET_U9_ATNET_3: I1.2, R18.2
NET_U9_ATNET_4: C26.2, R20.2
NET_U10_1: R26.1, R27.1, U10.1
NET_U10_3: R28.2, R29.1, U10.3
NET_U10_4: R25.1, U10.4, U13.2
NET_U11_1: R2.1, U11.1, U11.2
PROC_GPIO_TO_U2_FSYNC: U1.8, U2.11
PROC_GPIO_TO_U2_INT_B: U1.2, U2.12
PROC_SPI1_MISO: U1.22, U3.2
PROC_SPI1_MOSI: U1.23, U3.5
PROC_SPI1_NSS: R13.1, U1.20, U3.1
PROC_SPI1_SCK: U1.21, U3.6
PROC_USB_OTG_FS_DM: U1.44, U5.2, U6.3
PROC_USB_OTG_FS_DP: U1.45, U5.3, U6.2
PROC_USB_OTG_FS_ID: U1.43, U5.4
PROC_USB_OTG_FS_VBUS: U1.42, U5.1, U6.4
VCC_S1_17V0: C23.1, C30.1, C31.1, J1.1, R23.2, U9.9
VCC_TIER1_3V3: C1.1, C2.1, C3.1, C4.1, C5.1, C6.1, C7.1, C8.1, C16.1, C17.1, C18.1, C19.1, C29.1, C32.1, F1.2, I1.2, R4.2, R5.2, R6.2, R7.2, R8.2, R10.2, R11.2, R12.2, R13.2, R14.2, R15.2, R16.2, R18.2, R25.2, R26.2, R28.1, U1.1, U1.19, U1.32, U1.48, U1.64, U2.1, U2.8, U2.13, U3.8, U4.1, U10.6, U13.5
